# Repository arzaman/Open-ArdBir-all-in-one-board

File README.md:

# Open-ArdBir-all-in-one-board
Repository for HW design file (PCB, schematic)  of ArdBir all-in-one board

Open Ardbir is an open source SW (up to release 2.8.3) to control and automate beer brewing process
The SW have been developed based on Arduino UNO board (Atmega328 MCU) with few surroundings HW component to drive and interface external elements (PUMP, Heating element , LCD, push button etc.)

There are few open source HW board available supporting the SW either designed as  shield on top of Arduino Board, in this repository you can find all the CAD design file in order to build an "all-in-one" board that supports microcontroller Atmega328 (Arduino UNO) , all the surrounding componets (power, quartz, USB..) and the specific HW for interfacing brewing elements

The final result will be like this

PCB design

Schema

Enjoy and feel free to use and fork the project

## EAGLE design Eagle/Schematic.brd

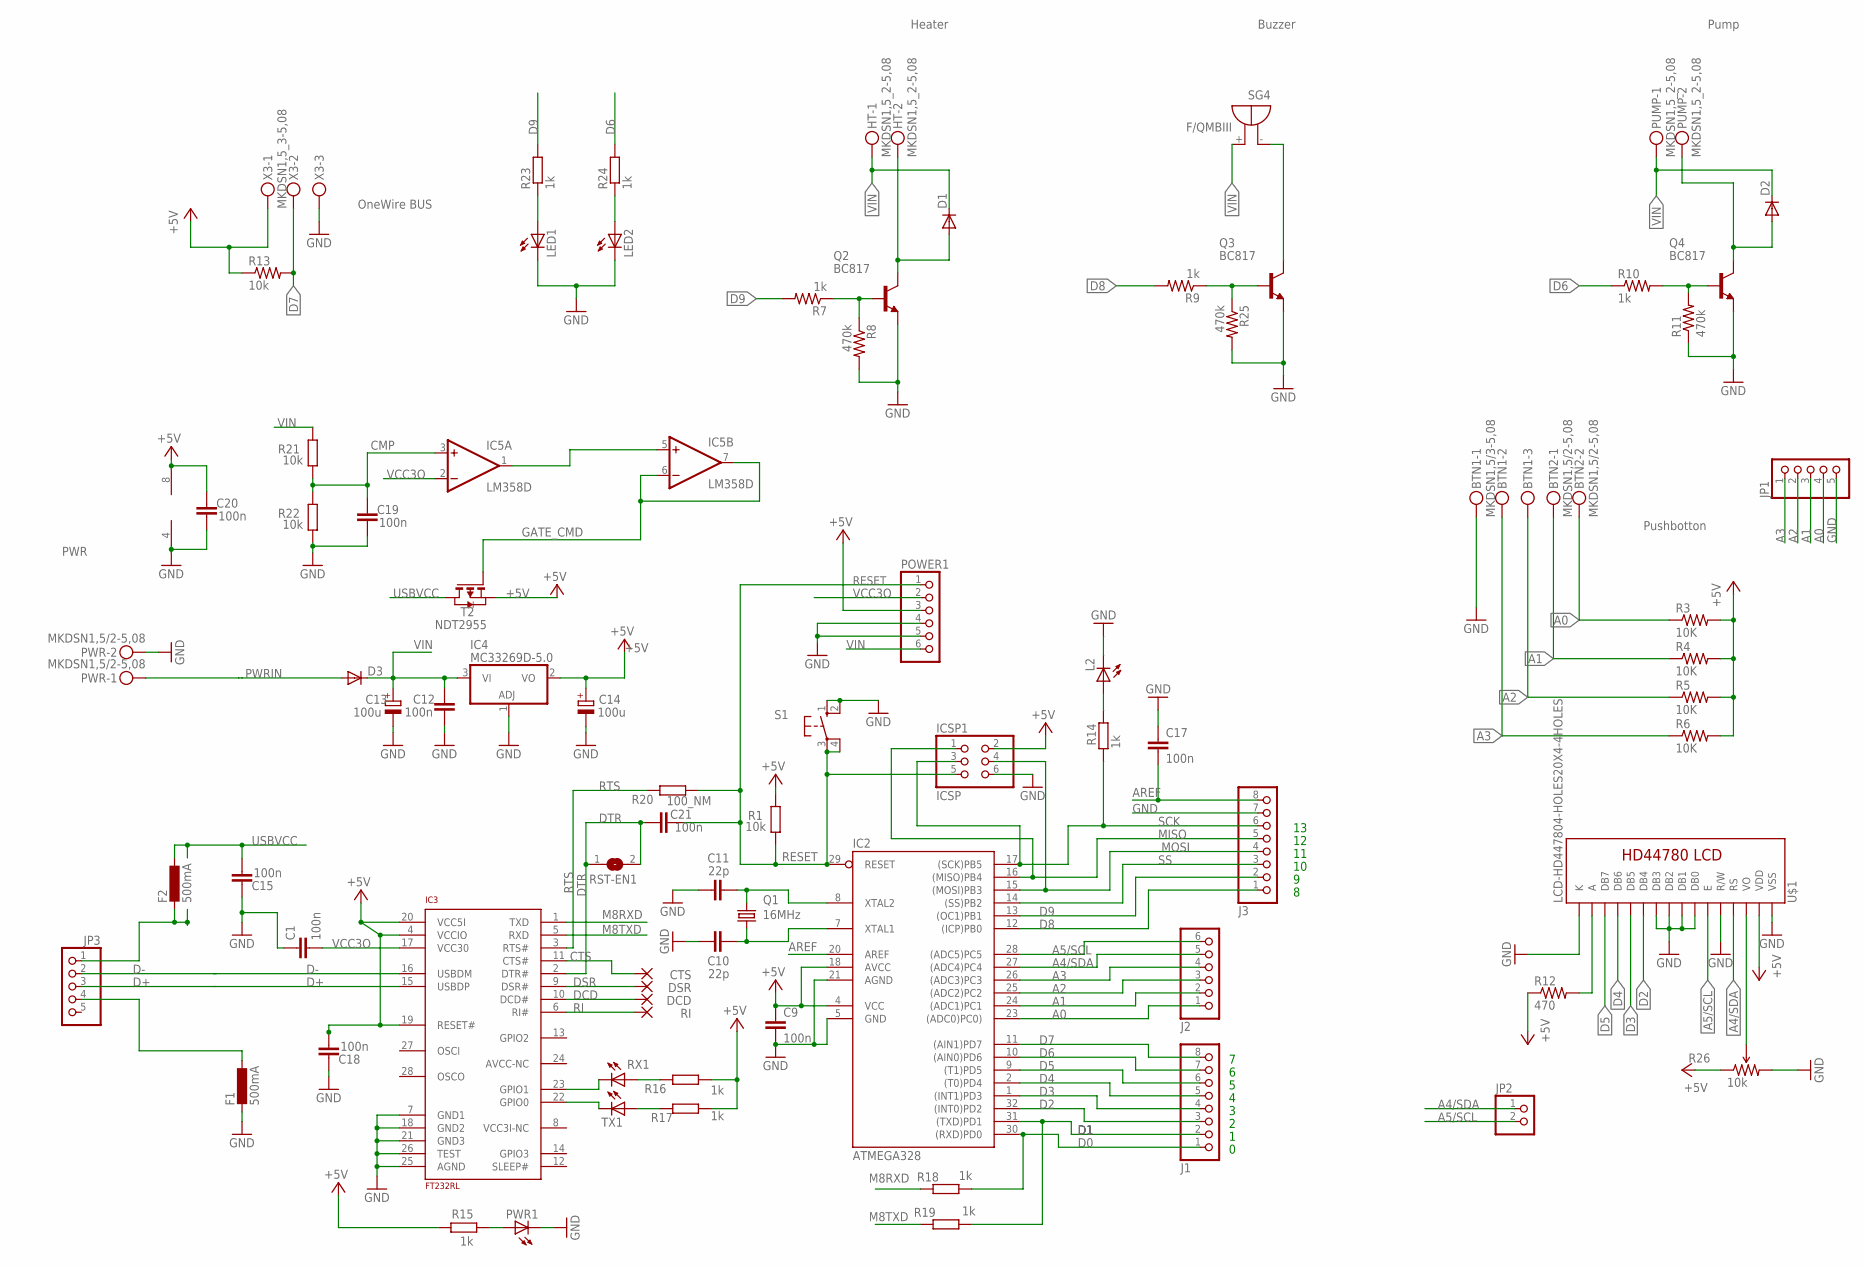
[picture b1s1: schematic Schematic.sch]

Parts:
BTN1: MKDSN1,5/3-5,08
BTN2: MKDSN1,5/2-5,08
C1, C9, C12, C15, C17, C18, C19, C20, C21: 100n; C0603
C10, C11: 22p; C0603
C13, C14: 100u; PANASONIC_D
CTS: SMD2; SMD1,27-2,54
D1, D2, D3: DIODE-SMB; SMB
DCD: SMD2; SMD1,27-2,54
DSR: SMD2; SMD1,27-2,54
F1, F2: 500mA; L1812
HT: MKDSN1,5_2-5,08; MKDSN1,5-2-5,08
IC2: ATMEGA328; TQFP32-08
IC3: FT232RL; SSOP28
IC4: MC33269D-5.0; DPACK
IC5: LM358D; SO08
ICSP1: ICSP; 2X03
J1, J3: PINHD-1X8; 1X08
J2: PINHD-1X6; 1X06
JP1, JP3: PINHD-1X5/90; 1X05/90
JP2: PINHD-1X2/90; 1X02/90
L2: LEDSML0805; SML0805
LED1, LED2: LED5MM
POWER1: PINHD-1X6; 1X06
PUMP: MKDSN1,5_2-5,08; MKDSN1,5-2-5,08
PWR: MKDSN1,5/2-5,08
PWR1: LEDSML0805; SML0805
Q1: 16MHz; HC49/S
Q2, Q3, Q4: BC817; SOT23-BEC
R1, R13, R21, R22: 10k; R0603
R3, R4, R5, R6: 10K; R0603
R7, R9, R10, R14, R15, R16, R17, R18, R19, R23, R24: 1k; R0603
R8, R11, R25: 470k; R0603
R12: 470; R1206
R20: 100_NM; R0603
R26: 10k; TRIMPOT-5MM
RI: SMD2; SMD1,27-2,54
RST-EN1: SJ
RX1: LEDSML0805; SML0805
S1: 10-XX; B3F-10XX
SG4: F/QMBIII
T2: NDT2955; SOT223
TX1: LEDSML0805; SML0805
U$1: LCD-HD447804-HOLES20X4-4HOLES; LCD-20X4-4HOLES
X3: MKDSN1,5_3-5,08; MKDSN1,5-3-5,08

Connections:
+5V: C9.1, C14.+, C18.1, C20.2, IC2.4 (VCC), IC2.18 (AVCC), IC3.4 (VCCIO), IC3.19 (RESET#), IC3.20 (VCC5I), IC4.2 (VO), IC5.8 (V+), ICSP1.2, POWER1.3, R1.2, R3.2, R4.2, R5.2, R6.2, R12.1, R13.1, R15.1, R16.2, R17.2, R26.A (CCW), T2.3 (S), U$1.P$2 (VDD), X3.1
A0: BTN2.2, IC2.23 ((ADC0)PC0)), J2.1, JP1.4, R3.1
A1: BTN2.1, IC2.24 ((ADC1)PC1), J2.2, JP1.3, R4.1
A2: BTN1.3, IC2.25 ((ADC2)PC2), J2.3, JP1.2, R5.1
A3: BTN1.2, IC2.26 ((ADC3)PC3), J2.4, JP1.1, R6.1
A4/SDA: IC2.27 ((ADC4)PC4), J2.5, JP2.1, U$1.P$4 (RS)
A5/SCL: IC2.28 ((ADC5)PC5), J2.6, JP2.2, U$1.P$6 (E)
AREF: C17.2, IC2.20 (AREF), J3.8
CMP: C19.2, IC5.3 (+IN), R21.1, R22.2
CTS: CTS.1, IC3.11 (CTS#)
D0: IC2.30 ((RXD)PD0), J1.1, R18.1
D1: IC2.31 ((TXD)PD1), J1.2, R19.1
D2: IC2.32 ((INT0)PD2), J1.3, U$1.P$11 (DB4)
D3: IC2.1 ((INT1)PD3), J1.4, U$1.P$12 (DB5)
D4: IC2.2 ((T0)PD4), J1.5, U$1.P$13 (DB6)
D5: IC2.9 ((T1)PD5), J1.6, U$1.P$14 (DB7)
D6: IC2.10 ((AIN0)PD6), J1.7, R10.1, R24.2
D7: IC2.11 ((AIN1)PD7), J1.8, R13.2, X3.2
D8: IC2.12 ((ICP)PB0), J3.1, R9.2
D9: IC2.13 ((OC1)PB1), J3.2, R7.2, R23.2
D+: IC3.15 (USBDP), JP3.3
D-: IC3.16 (USBDM), JP3.2
DCD: DCD.1, IC3.10 (DCD#)
DSR: DSR.1, IC3.9 (DSR#)
DTR: C21.1, IC3.2 (DTR#), RST-EN1.1, RST-EN1.2
GATE_CMD: IC5.6 (-IN), IC5.7 (OUT), T2.1 (G)
GND: BTN1.1, C1.1, C9.2, C10.1, C11.1, C12.1, C13.-, C14.-, C15.2, C17.1, C18.2, C19.1, C20.1, F1.2, IC2.5 (GND), IC2.21 (AGND), IC3.7 (GND1), IC3.18 (GND2), IC3.21 (GND3), IC3.25 (AGND), IC3.26 (TEST), IC4.1 (ADJ), IC5.4 (V-), ICSP1.6, J3.7, JP1.5, L2.C, LED1.K (C), LED2.K (C), POWER1.4, POWER1.5, PWR.2, PWR1.C, Q2.E, Q3.E, Q4.E, R8.2, R11.1, R22.1, R25.2, R26.C (CW), S1.1 (S), S1.2 (S1), U$1.P$1 (VSS), U$1.P$5 (R/W), U$1.P$7 (DB0), U$1.P$8 (DB1), U$1.P$9 (DB2), U$1.P$10 (DB3), U$1.P$16 (K), X3.3
M8RXD: IC3.1 (TXD), R18.2
M8TXD: IC3.5 (RXD), R19.2
MISO: IC2.16 ((MISO)PB4), ICSP1.1, J3.5
MOSI: IC2.15 ((MOSI)PB3), ICSP1.4, J3.4
unnamed: F1.1, JP3.4
unnamed: D1.A, HT.2, Q2.C
unnamed: Q2.B, R7.1, R8.1
unnamed: D2.A, PUMP.2, Q4.C
unnamed: Q3.C, SG4.- (+)
unnamed: Q3.B, R9.1, R25.1
unnamed: Q4.B, R10.2, R11.2
unnamed: R12.2, U$1.P$15 (A)
unnamed: R26.B (WIPER), U$1.P$3 (VO)
unnamed: LED1.A, R23.1
unnamed: LED2.A, R24.1
unnamed: C10.2, IC2.7 (XTAL1), Q1.1
unnamed: C11.2, IC2.8 (XTAL2), Q1.2
unnamed: PWR1.A, R15.2
unnamed: IC3.23 (GPIO1), RX1.C
unnamed: IC3.22 (GPIO0), TX1.C
unnamed: R16.1, RX1.A
unnamed: R17.1, TX1.A
unnamed: F2.2, JP3.1
unnamed: L2.A, R14.1
unnamed: IC5.1 (OUT), IC5.5 (+IN)
PWRIN: D3.A, PWR.1
RESET: C21.2, IC2.29 (RESET), ICSP1.5, POWER1.1, R1.1, R20.2, S1.3, S1.4 (P1)
RI: IC3.6 (RI#), RI.1
RTS: IC3.3 (RTS#), R20.1
SCK: IC2.17 ((SCK)PB5), ICSP1.3, J3.6, R14.2
SS: IC2.14 ((SS)PB2), J3.3
USBVCC: C15.1, F2.1, T2.2 (D), T2.4 (D)
VCC3O: C1.2, IC3.17 (VCC30), IC5.2 (-IN), POWER1.2
VIN: C12.2, C13.+, D1.C, D2.C, D3.C, HT.1, IC4.3 (VI), POWER1.6, PUMP.1, R21.2, SG4.+ (-)

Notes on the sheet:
Pushbotton
Heater
Buzzer
Pump
PWR
OneWire BUS

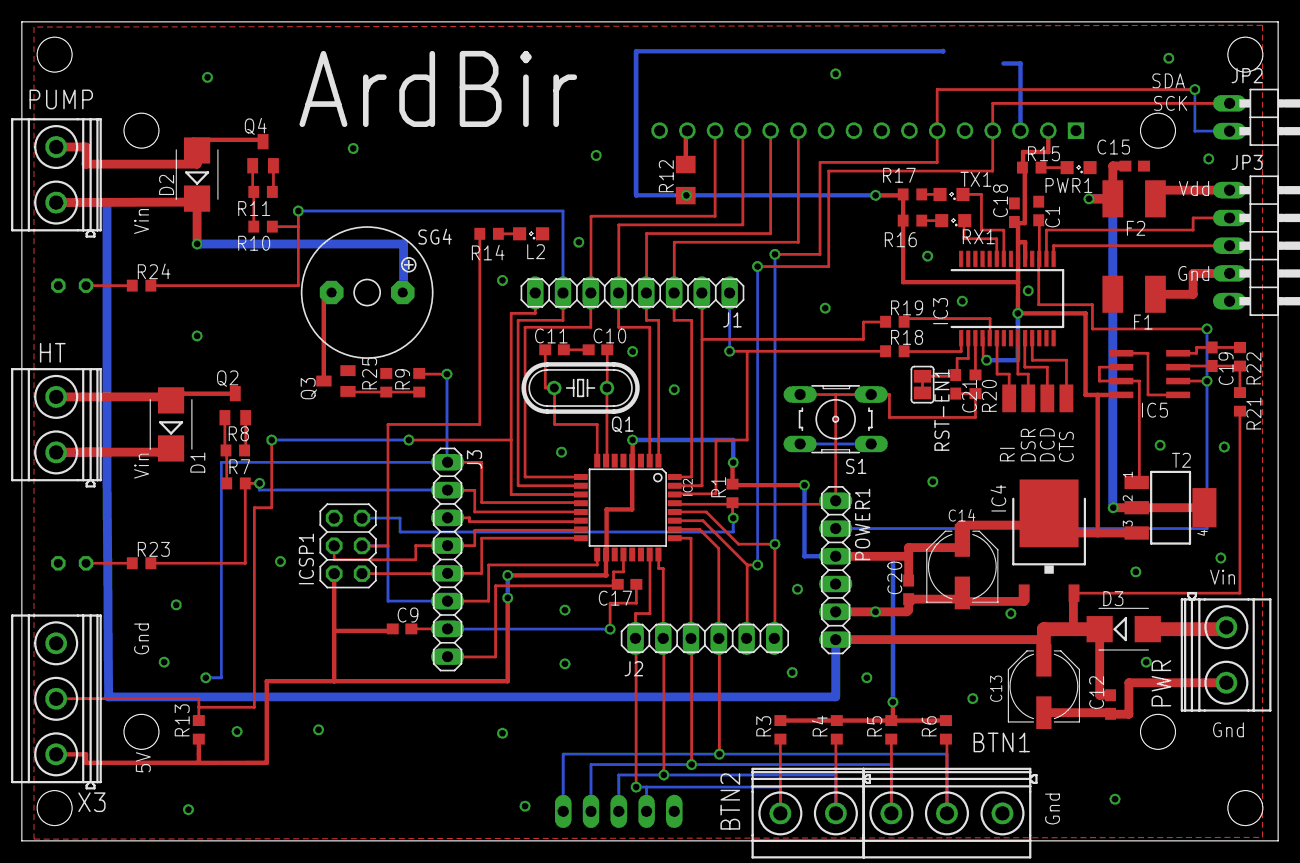
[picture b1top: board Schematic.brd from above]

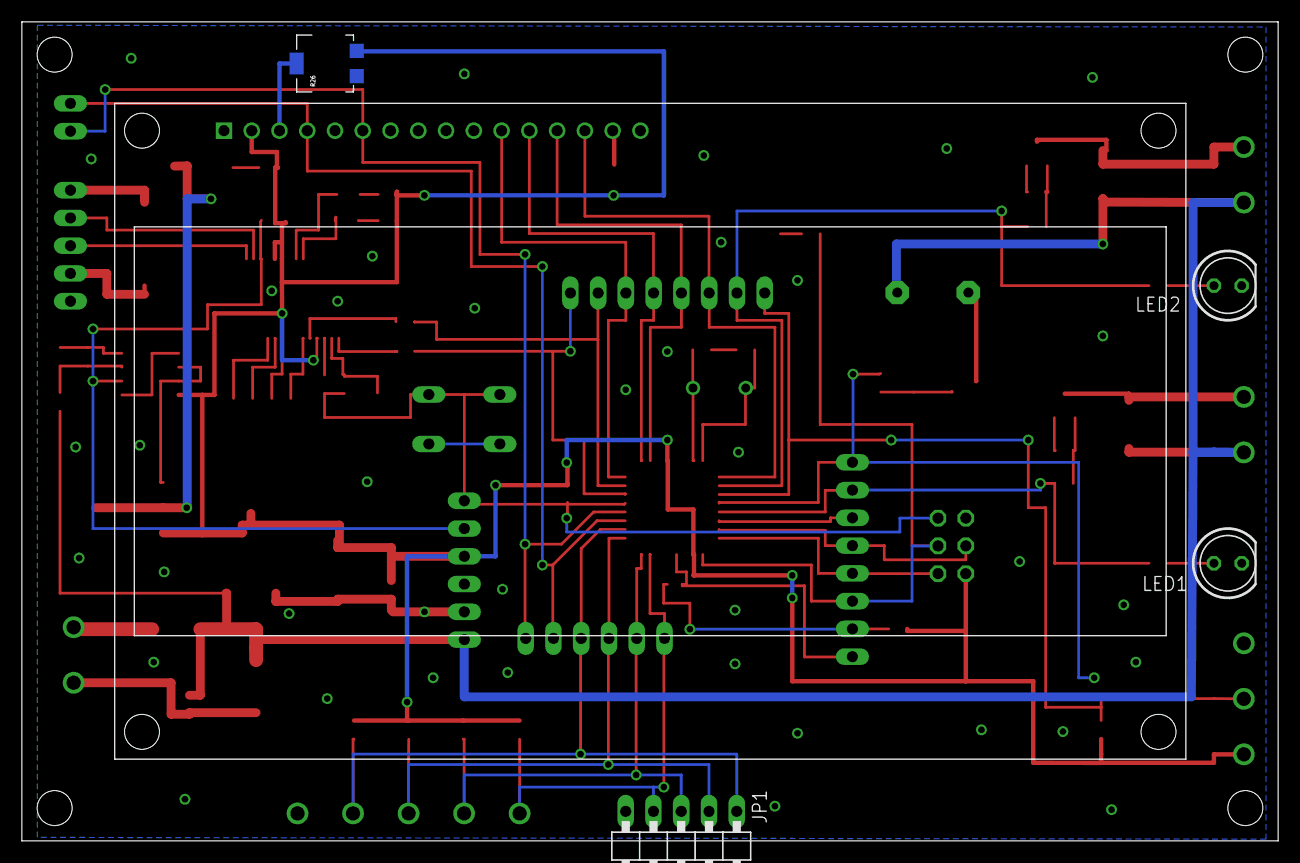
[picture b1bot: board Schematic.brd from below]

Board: 2 copper layers, 114.9 x 74.9 mm, 80 parts (5 on the bottom side), 61 nets.

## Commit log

2016-01-12 all-in-one
2016-01-12 license

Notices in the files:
parts and their libraries:
SparkFun-Electromechanical: Licensing: Creative Commons ShareAlike 4.0 International - https://creativecommons.org/licenses/by-sa/4.0
